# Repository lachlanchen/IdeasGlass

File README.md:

[English](README.md) · [العربية](i18n/README.ar.md) · [Español](i18n/README.es.md) · [Français](i18n/README.fr.md) · [日本語](i18n/README.ja.md) · [한국어](i18n/README.ko.md) · [Tiếng Việt](i18n/README.vi.md) · [中文 (简体)](i18n/README.zh-Hans.md) · [中文（繁體）](i18n/README.zh-Hant.md) · [Deutsch](i18n/README.de.md) · [Русский](i18n/README.ru.md)

# IdeasGlass

*A wearable AI glass that turns ideas into actions, income, and creative momentum.*

> Voice-first wearable AI pipeline: capture from ESP32 glasses, process in FastAPI, and monitor/control via a live PWA dashboard.

| Lane | Purpose |
|---|---|
| 🎙️ Wearable capture | ESP32 glasses send audio, photos, and telemetry in near-real-time |
| 🧠 Backend intelligence | FastAPI ingests streams, transcribes, segments, and persists metadata |
| 🖥️ Dashboard | PWA shows live waveform, transcripts, and device/account status |

<div align="center">

  <br/>
  <sub>App UI (left) · Hardware (right)</sub>
</div>

Explore community experiments at <a href="https://onlyideas.art">onlyideas.art</a>.

## 🚀 Overview

IdeasGlass is an AI-first wearable system for voice-first idea capture and execution. In this repository, the primary runtime path is:

- `backend/glass/` for FastAPI APIs, WebSocket ingest, Whisper-based transcription, and the installable PWA dashboard.
- `IdeaGlass/firmware/ideasglass_arduino/IdeasGlassClient/` for XIAO ESP32S3 firmware streaming telemetry/audio/photos.

If you are new to this repo, start there first.

## 📚 Table of Contents

- [🚀 Overview](#-overview)
- [✨ Why IdeasGlass](#-why-ideasglass)
- [🧩 Features](#-features)
- [🔄 Sample Workflow](#-sample-workflow)
- [🗂️ Project Structure](#-project-structure)
- [🧰 Prerequisites](#-prerequisites)
- [⚙️ Installation](#️-installation)
- [▶️ Usage](#️-usage)
- [🛠️ Configuration](#️-configuration)
- [🧪 Examples](#-examples)
- [🧭 Development Notes](#-development-notes)
- [🆘 Troubleshooting](#️-troubleshooting)
- [🌐 Ecosystem Links](#-ecosystem-links)
- [🙏 Acknowledgements](#-acknowledgements)
- [🛣️ Roadmap](#️-roadmap)
- [🤝 Contribution](#-contribution)
- [❤️ Support](#-support)
- [📄 License](#-license)

### At a glance

| Area | Primary location | What it does |
|---|---|---|
| Backend API + PWA | `backend/glass/` | FastAPI endpoints, WebSocket ingest/fanout, transcription, dashboard |
| Firmware | `IdeaGlass/firmware/ideasglass_arduino/IdeasGlassClient/` | ESP32 capture/streaming client |
| Bridge notes | `references/ideasglass_bridge.md` | TLS/WAN reliability notes and deployment field tips |
| README translations | `i18n/` | Multilingual docs synced from the canonical README |

## ✨ Why IdeasGlass

IdeasGlass is an AI-first wearable built for people who live in streams of ideas. It captures, translates, organizes, and executes on creativity the moment inspiration strikes, whether you are narrating a concept in motion or hosting a live session.

## 🧩 Features

### Product vision features

- **Creation-native hardware** – lightweight glasses and wearable inputs, tuned for voice-first capture plus subtle gesture shortcuts.
- **Instant translation** – real-time language detection/translation so you can ideate across teams or audiences without switching tools.
- **EchoMind co-pilot** – tight pairing with `chat.lazying.art` for brainstorming, script drafting, and multilingual content coaching.
- **Channel autopilot** – drafts outlines, long-form scripts, short-form hooks, and schedules uploads to YouTube or other feeds.
- **Highlights & reels** – auto-selects moments, generates thumbnails, subtitles, and social-ready clips.
- **Income layer** – connects to LazyingArt Coin for tipping, credit payouts, and conversion to on-chain assets.
- **Spending & focus** – tracks operational spend, surfaces profitable formats, and distills your personal strengths into next projects.

### Repository/runtime features

- FastAPI backend with REST + WebSocket endpoints for ingest (`/api/v1/audio`, `/ws/audio-ingest`) and live stream fanout (`/ws/stream`).
- Deterministic audio segmentation (default ~15 s with overlap) into `backend/glass/audio_segments/`.
- Optional openai-whisper streaming transcripts with configurable latency thresholds.
- Optional Postgres persistence (`DATABASE_URL`) for messages, photos, chunks, segments, transcripts.
- PWA dashboard with live waveform, transcript updates, and install support on desktop/mobile.
- Arduino firmware support for XIAO ESP32S3 Sense camera + mic flows.

## 🔄 Sample Workflow

1. **Capture** – Speak or sketch a concept; IdeasGlass transcribes, translates, and tags the intent.
2. **Co-create** – EchoMind refines the idea, drafts scripts, and suggests CTAs tailored for each platform.
3. **Publish** – The channel agent auto-produces highlight videos, gallery images, and uploads them with metadata.
4. **Monetize** – Credits route through LazyingArt Coin (`coin.lazying.art`) and payouts sync with your preferred wallets.
5. **Reflect** – Spending, reach, and engagement dashboards surface what to double down on next.

## 🗂️ Project Structure

```text
IdeasGlass/
├── README.md
├── i18n/                                  # README translations
├── backend/
│   ├── glass/                             # Primary FastAPI + PWA backend
│   │   ├── app.py
│   │   ├── serve.py
│   │   ├── requirements.txt
│   │   ├── static/
│   │   ├── tools/
│   │   └── audio_segments/
│   ├── tornado_app/                       # Secondary/parallel ingest backend path
│   ├── memo/
│   ├── memo_legacy/
│   └── ngrok_bridge/
├── IdeaGlass/firmware/ideasglass_arduino/
│   ├── IdeasGlassClient/
│   ├── config.h
│   ├── WifiTest/WifiTest.ino
│   ├── wifi_credentials.example.h
│   └── README.md
├── references/ideasglass_bridge.md        # Bridge + deployment notes
├── docs/                                  # Additional site/docs assets
├── development_plan/
├── app/
├── ops/observability/
├── ios-app-example/
├── figs/
├── seeed_studio_xiao_esp32s3_dev/
└── .auto-readme-work/
```

## 🧰 Prerequisites

- Python 3.10+
- `pip` (or conda environment with compatible Python)
- Optional: NVIDIA GPU + CUDA/cuDNN for faster Whisper inference
- Optional: PostgreSQL for persistence
- For firmware: Arduino IDE or `arduino-cli`, Seeed XIAO ESP32S3 Sense, PSRAM enabled

| Component | Requirement | Notes |
|---|---|---|
| Backend runtime | Python 3.10+, `pip` | Use venv or conda (`glass`) |
| GPU acceleration (optional) | NVIDIA + CUDA/cuDNN | Improves Whisper latency |
| Persistence (optional) | PostgreSQL | Enabled via `DATABASE_URL` |
| Firmware toolchain | Arduino IDE / `arduino-cli` | Use XIAO ESP32S3 profile with PSRAM |

## ⚙️ Installation

### Backend dependencies

```bash
cd backend/glass
python -m venv .venv
source .venv/bin/activate
pip install -r requirements.txt
```

### Firmware prerequisites

- Copy `IdeaGlass/firmware/ideasglass_arduino/wifi_credentials.example.h` to `wifi_credentials.h` (recommended) and set SSID/password.
- In Arduino IDE, use board `ESP32 -> XIAO_ESP32S3` with `PSRAM: OPI PSRAM`.
- Partition scheme: `Default with spiffs (3MB APP/1.5MB SPIFFS)` or `Maximum APP` when filesystem is not needed.

## ▶️ Usage

### Run backend (uvicorn)

```bash
IDEASGLASS_WHISPER_MODEL=base IDEASGLASS_WHISPER_DEVICE=cuda \
uvicorn backend.glass.app:app \
  --host 0.0.0.0 \
  --port 8765 \
  --proxy-headers \
  --forwarded-allow-ips="*" \
  --reload
```

### Run backend (helper)

```bash
python backend/glass/serve.py --whisper-model base --whisper-device cuda --reload
```

### Open dashboard

- `http://localhost:8765/`
- `http://localhost:8765/healthz`

| Endpoint | Purpose |
|---|---|
| `/` | Main dashboard (PWA-capable UI) |
| `/healthz` | Backend liveness check |
| `/ws/audio-ingest` | Device ingest WebSocket |
| `/ws/stream` | Live stream fanout to dashboard clients |

### Login and bind your device

1. Register or login from the dashboard Settings/Account area.
2. Bind your device ID in the `Bind device` field.
3. Only bound devices will stream to your account.

Generate a device ID + QR image:

```bash
python backend/glass/tools/generate_device_id.py --out logs/device-id.png
```

Bind through API (cookie session required):

```bash
curl -X POST http://localhost:8765/api/v1/devices/bind \
  -H 'Content-Type: application/json' \
  -d '{"device_id":"<your-device-id>"}' \
  -b cookies.txt -c cookies.txt
```

Verify current account and bound devices:

```bash
curl -s http://localhost:8765/api/v1/auth/me -b cookies.txt -c cookies.txt | jq
```

Optional migration (rename historical data to a new device ID):

```bash
curl -X POST http://localhost:8765/api/v1/devices/rename \
  -H 'Content-Type: application/json' \
  -d '{"from_id":"old-id","to_id":"<your-device-id>"}' \
  -b cookies.txt -c cookies.txt
```

### Firmware build/upload (Arduino CLI)

```bash
FQBN='esp32:esp32:XIAO_ESP32S3:PartitionScheme=default_8MB,PSRAM=opi'
SKETCH='IdeaGlass/firmware/ideasglass_arduino/IdeasGlassClient'
PORT='/dev/ttyACM0'

bin/arduino-cli compile --fqbn "$FQBN" "$SKETCH"
bin/arduino-cli upload -p "$PORT" --fqbn "$FQBN" "$SKETCH"
```

If port is busy: `fuser -k /dev/ttyACM0`.
If permission denied: `sudo usermod -aG dialout $USER` then re-login (or temporary `sudo chmod a+rw /dev/ttyACM0`).

### Firmware power UX (XIAO ESP32S3)

- Hold the button ~0.8 s at power-up to boot.
- Hold ~2.5 s while running to enter deep sleep.
- Short press while running still triggers capture.

## 🛠️ Configuration

### Core environment variables

- `DATABASE_URL`: optional Postgres DSN for persistent storage.
- `IDEASGLASS_WHISPER_MODEL`: `base` (default), `small`, `medium`, `large-v3`, `large-v3-turbo`.
- `IDEASGLASS_WHISPER_DEVICE`: `cuda` or `cpu`.
- `IDEASGLASS_WHISPER_FP16`: `1` for GPU mixed precision, `0` for CPU.
- `IDEASGLASS_TRANSCRIBE`: `1` (default) to enable transcription, `0` to disable.
- `IDEASGLASS_TRANSCRIPT_INTERVAL_MS`: rolling transcript interval.
- `IDEASGLASS_TRANSCRIPT_THRESHOLDS_MS`: comma-separated thresholds (default `3000,6000,15000`).

| Variable | Default / options | Effect |
|---|---|---|
| `DATABASE_URL` | unset by default | Enables Postgres persistence for account/device data |
| `IDEASGLASS_WHISPER_MODEL` | `base` (`small`, `medium`, `large-v3`, `large-v3-turbo`) | Controls accuracy vs latency |
| `IDEASGLASS_WHISPER_DEVICE` | `cuda` or `cpu` | Inference backend |
| `IDEASGLASS_WHISPER_FP16` | `1` GPU, `0` CPU-safe | Mixed precision control |
| `IDEASGLASS_TRANSCRIBE` | `1` | Toggle transcription pipeline |
| `IDEASGLASS_TRANSCRIPT_INTERVAL_MS` | runtime configured | Rolling transcript push interval |
| `IDEASGLASS_TRANSCRIPT_THRESHOLDS_MS` | `3000,6000,15000` | Progressive transcript emission thresholds |

Safe `DATABASE_URL` examples:

- `export DATABASE_URL="postgresql://<db_user>@localhost/ideasglass_db"` (peer/local auth)
- `export DATABASE_URL="postgresql://<db_user>:<db_password>@localhost/ideasglass_db"` (password auth)

### Audio gain and segmentation knobs

- `IDEASGLASS_GAIN_TARGET` (default `0.032`)
- `IDEASGLASS_GAIN_MAX` (default `1.8`)
- `IDEASGLASS_GAIN_MIN_RMS` (default `0.008`)
- `IDEASGLASS_SPEECH_RMS` (default `0.03`)
- `IDEASGLASS_SPEECH_MARGIN` (default `0.005`)
- `IDEASGLASS_SEGMENT_TARGET_MS` (default `15000`)
- `IDEASGLASS_SEGMENT_OVERLAP_MS` (default `2000`)
- `IDEASGLASS_SEGMENT_GAIN_TARGET` (defaults to chunk gain target)

| Audio knob | Default | Purpose |
|---|---|---|
| `IDEASGLASS_GAIN_TARGET` | `0.032` | Target RMS normalization |
| `IDEASGLASS_GAIN_MAX` | `1.8` | Upper clamp for gain amplification |
| `IDEASGLASS_GAIN_MIN_RMS` | `0.008` | Floor to avoid amplifying near-silence |
| `IDEASGLASS_SPEECH_RMS` | `0.03` | Speech activity RMS baseline |
| `IDEASGLASS_SPEECH_MARGIN` | `0.005` | Margin around speech threshold |
| `IDEASGLASS_SEGMENT_TARGET_MS` | `15000` | Segment length target |
| `IDEASGLASS_SEGMENT_OVERLAP_MS` | `2000` | Segment overlap for continuity |
| `IDEASGLASS_SEGMENT_GAIN_TARGET` | inherits chunk gain | Segment-level normalization target |

### Model prefetch (optional)

```bash
python backend/glass/tools/prefetch_whisper_models.py \
  --models tiny,base,small,medium,large-v3 \
  --device cuda \
  --fp16 1
```

## 🧪 Examples

### Generate and bind a device ID

```bash
python backend/glass/tools/generate_device_id.py --out logs/device-id.png
```

Then set `kDeviceId` in:

- `IdeaGlass/firmware/ideasglass_arduino/IdeasGlassClient/IdeasGlassClient.ino`

Dashboard flow:

1. Register/login in Settings.
2. Bind the device in the Account panel.
3. Only bound devices stream to your account.

### REST ingest examples

```bash
curl -X POST http://localhost:8765/api/v1/messages \
  -H 'Content-Type: application/json' \
  -d '{"device_id":"dev-001","message":"hello from curl"}'
```

```bash
curl -X POST http://localhost:8765/api/v1/messages \
  -H 'Content-Type: application/json' \
  -d '{
    "device_id":"dev-001",
    "message":"photo demo",
    "photo_base64":"'"$(base64 -w0 sample.jpg)'"',
    "photo_mime":"image/jpeg"
  }'
```

```bash
rec --bits 16 --channels 1 --rate 16000 -c 1 -b 16 -e signed-integer temp.raw trim 0 0.25
curl -X POST http://localhost:8765/api/v1/audio \
  -H 'Content-Type: application/json' \
  -d '{
    "device_id":"dev-001",
    "sample_rate":16000,
    "bits_per_sample":16,
    "duration_ms":250,
    "rms":0.05,
    "audio_base64":"'"$(base64 -w0 temp.raw)'"'
  }'
```

```bash
curl http://localhost:8765/api/v1/audio/segments | jq '.[0]'
curl -o latest.wav http://localhost:8765/api/v1/audio/segments/<segment-id>
```

## 🧭 Development Notes

### Focus area

This repo contains multiple backend tracks. Current contributor guidance and runtime focus is `backend/glass/` unless otherwise requested.

### Static/syntax check

```bash
python -m compileall backend/glass/app.py
```

### Developer docs

- [IdeasGlass Object Analysis](OmiGlass/docs/ideasglass_analysis.mdx)
- [Arduino Hardware Blueprint](OmiGlass/docs/ideasglass_arduino_hardware.md)
- [Multi-platform App / PWA Plan](OmiGlass/docs/ideasglass_pwa_plan.md)
- [Bridge & Arduino HTTPS Client](docs/ideasglass_bridge.md)

> Note: In the current repository snapshot, some historical links above appear to have moved (for example, bridge notes now exist at `references/ideasglass_bridge.md`). The original links are preserved as canonical README content.

### Quick device binding (preserved workflow)

- Generate ID (in conda `glass`): `python backend/glass/tools/generate_device_id.py`
- Set it in firmware: `IdeaGlass/firmware/ideasglass_arduino/IdeasGlassClient/IdeasGlassClient.ino` (`kDeviceId`)
- Run backend and open `http://localhost:8765`, register/login, then bind the device ID in the Account panel

## 🆘 Troubleshooting

- **Port already in use:** run backend on another port and update client settings.
- **Serial port busy:** `fuser -k /dev/ttyACM0`.
- **Linux serial permission denied:** `sudo usermod -aG dialout $USER` and re-login.
- **Postgres unavailable:** backend can run without DB for partial functionality; verify `DATABASE_URL` and restart.
- **Whisper performance issues:** use smaller models (`base`/`small`) or disable transcription via `IDEASGLASS_TRANSCRIBE=0`.
- **TLS/time sync instability on ESP32:** verify Wi-Fi, NTP availability (UDP/123), and cert/host settings; see `references/ideasglass_bridge.md` for detailed field notes.
- **No live waveform updates:** check backend logs and browser console for `[IdeasGlass][wave]` traces and confirm `/ws/stream` connectivity.

## 🌐 Ecosystem Links

| Brand | Purpose | Link |
|---|---|---|
| 🧠 EchoMind | Multilingual AI companion for learning and creation | [chat.lazying.art](https://chat.lazying.art) |
| 🌱 OnlyIdeas | Research-to-product community for bold concepts | [onlyideas.art](https://onlyideas.art) |
| 💸 LazyEarn | Automations to turn small wins into income | [earn.lazying.art](https://earn.lazying.art) |
| 📚 LazyLearn | Physics & chemistry tracks and notebooks | [learn.lazying.art](https://learn.lazying.art) |
| 🤖 IdeasRobot | Agent that turns ideas into drafts, tasks, and posts | [robot.lazying.art](https://robot.lazying.art) |
| 👓 IdeasGlass | Capture, translate, and auto-produce highlight reels | [glass.lazying.art](https://glass.lazying.art) |
| 🪙 LazyingArt Coin | Rewards and payouts bridging contributions and on-chain value | [coin.lazying.art](https://coin.lazying.art) |
| 🧪 IDEAS | Notebook of research notes and essays | [ideas.onlyideas.art](https://ideas.onlyideas.art) |
| 🎨 LazyingArt | Studio behind OnlyIdeas, EchoMind, LazyEdit, and IdeasGlass | [lazying.art](https://lazying.art) |

## 🙏 Acknowledgements

We stand on the shoulders of great open projects — thank you to:

- <a href="https://www.omi.me/?ref=LazyingArt" target="_blank" rel="noopener" style="display:inline-flex;align-items:center;justify-content:center;padding:0.45rem 1rem;border-radius:999px;background:#111827;color:#ffffff;font-weight:700;text-decoration:none;">Get OmiGlass (BasedHardware)</a>
  - **Referral Program** — Use coupon `LazyingArt` to save 10% (30% commission unlocks after 10 sales).

    <div style="display:flex;flex-wrap:wrap;gap:0.4rem;margin:0.3rem 0;">
      <a href="https://www.omi.me/?ref=LazyingArt" target="_blank" rel="noopener" style="display:inline-flex;align-items:center;justify-content:center;padding:0.45rem 1.1rem;border-radius:999px;background:#111827;color:#ffffff;font-weight:700;text-decoration:none;">Get OmiGlass with LazyingArt</a>
      <a href="https://discord.com/invite/8MP3b9ymvx?ref=LazyingArt" target="_blank" rel="noopener" style="display:inline-flex;align-items:center;justify-content:center;padding:0.45rem 1rem;border-radius:999px;background:#2563eb;color:#ffffff;font-weight:700;text-decoration:none;">Join Omi Discord</a>
      <a href="https://www.seeedstudio.com/Seeed-XIAO-BLE-Sense-nRF52840-p-5253.html" target="_blank" rel="noopener" style="display:inline-flex;align-items:center;justify-content:center;padding:0.45rem 1rem;border-radius:999px;background:#059669;color:#ffffff;font-weight:700;text-decoration:none;">Buy Seeed XIAO BLE Sense</a>
    </div>
- OpenAI Whisper: https://github.com/openai/whisper
- WhisperX: https://github.com/m-bain/whisperX
- Ollama: https://github.com/ollama/ollama

## 🛣️ Roadmap

- Harden and document the end-to-end audio streaming path across WAN/TLS environments.
- Continue improving transcript quality/latency tradeoffs (model/device/threshold presets).
- Expand device management and account-scoped multi-device workflows in the dashboard.
- Align or consolidate legacy/parallel backend tracks (`tornado_app`, `memo`, `memo_legacy`, `ngrok_bridge`) with the primary `backend/glass` path.
- Maintain and refresh multilingual README variants under `i18n/`.

## 🤝 Contribution

Contributions are welcome. For repository-specific workflow guidance, follow `AGENTS.md`.

Recommended local validation before opening a PR:

```bash
python -m compileall backend/glass/app.py
```

When submitting changes:

- Keep commit subjects short and action-driven (present tense).
- Mention relevant env vars (for example `IDEASGLASS_TRANSCRIPT_THRESHOLDS_MS`) in PR notes when behavior depends on them.
- Include testing evidence (backend logs, dashboard behavior, firmware output).
- Never commit secrets (`DATABASE_URL`, API tokens, credentials files).

## ❤️ Support

<!-- support:start -->

<!-- support:end -->

## 📄 License

No top-level `LICENSE` file was detected in this repository snapshot. Until an explicit license file is added, treat usage and redistribution as requiring maintainer approval.

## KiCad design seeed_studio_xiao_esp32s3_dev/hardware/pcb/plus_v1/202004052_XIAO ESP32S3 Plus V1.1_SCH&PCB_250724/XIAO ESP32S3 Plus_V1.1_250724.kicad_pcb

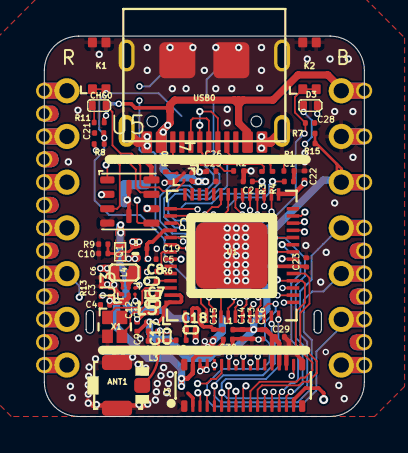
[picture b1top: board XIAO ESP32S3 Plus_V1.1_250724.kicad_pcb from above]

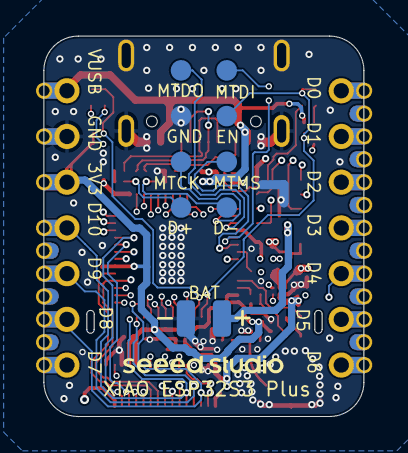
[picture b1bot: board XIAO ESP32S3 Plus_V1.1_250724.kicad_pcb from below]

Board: 6 copper layers, 17.8 x 21.1 mm, 70 parts (10 on the bottom side), 62 nets.

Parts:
ANT1: U.FL-R-SMT-1; U-FL3P-SMD-2.6X2.6X1.0MM
BAT0: VBAT; TP-80X40MIL
C1, C2, C20: DNP; C0201
C3, C9, C13, C16: 2.2uF; C0201
C4, C5, C6: 4.7uF; C0201
C7, C8: 12pF; C0201
C10, C21, C25, C26: 1uF; C0201
C11, C14, C15, C19, C22, C23, C29, C30: 100nF; C0201
C12: 10nF; C0201
C17: 1.2pF; C0201
C18: 1.8pF; C0201
C28: 10pF; C0201
CHG0: RED; LED-0402
D2: LMBR4010BST5G; DFN1006-2L
D3: Yellow; LED-0402
GND0: GND; TP-80X40MIL
J3: 30pin; BTB30-0.4-7.52X2.97X1.14
K1, K2: SKTAAAE010/311021459; SW4-SMD-2.8-2.6X1.6X0.53MM
L1: 2nH; L0201
L2: 3.3nH; L0201
L3: DNP; L0201
L4: 470nH; L0603
L5: 24nH; L0201
Q1: PMOS_1.00.60.35MM; PMOS_1.0*0.6*0.35MM
R1, R2: 5.1K; R0201
R3, R4: 22R; R0201
R6: 499R; R0201
R7, R8, R11: 10K; R0201
R9: 100K; C0201
R10: 220K; R0201
R13: 249K; R0201
R15: 1.5K; R0201
TP1, TP2, TP3, TP4, TP5, TP6, TP7, TP8: TEST-POINT'4545'; TP-D45MIL
U1: MCU-ESP32-S3; QFN56G-0.4-7X7MM
U2: XIAO-HALF-HOLE-23P; MOUDLE23P-XIAO-HALF-HOLE
U3: SGM6029CYG/TR; BGA6-0.35-0.85X1.2X0.4MM
U4: SGM40567-4.2XG/TR; WLCSP-0.4-0.92X1.16X0.4MM
U5: PY25Q128HA-DFH-IR; USON8-0.8-3X3X0.55MM
USB0: UBF31-0171; USB2.0-TYPE-C
X1: 40MHz; X4-SMD-1.6X1.2X0.35MM

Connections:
/D0/A0: U1.6 (GPIO1), U2.1 (GPIO1_D0/A0)
/D1/A1: U1.7 (GPIO2), U2.2 (GPIO2_D1/A1)
/D2/A2: J3.2, U1.8 (GPIO3), U2.3 (GPIO3_D2/A2)
/D3/A3: U1.9 (GPIO4), U2.4 (GPIO4_D3/A3)
/D4/A4/I2C_SDA: U1.10 (GPIO5), U2.5 (GPIO5_D4/A4/I2C_SDA)
/D5/A5/I2C_SCL: U1.11 (GPIO6), U2.6 (GPIO6_D5/A5/I2C_SCL)
/D6/TX: R6.2, U2.7 (U0TXD_D6/TX)
/D7/RX: U1.50 (U0RXD), U2.8 (U0RXD_D7/RX)
/D8/A8/SCK: J3.3, U1.12 (GPIO7), U2.9 (GPIO7_D8/A8/SCK)
/D9/A9/MISO: J3.4, U1.13 (GPIO8), U2.10 (GPIO8_D9/A9/MISO)
/D10/A10/MOSI: J3.5, U1.14 (GPIO9), U2.11 (GPIO9_D10/A10/MOSI)
/EN: C21.2, K1.1 (A0), K1.3 (A1), R8.1, TP6.T, U1.4 (CHIP_PU)
/ESP_USB_D+: C1.2, R4.2, TP8.T, U1.26 (GPIO20)
/ESP_USB_D-: C2.2, R3.2, TP7.T, U1.25 (GPIO19)
/GPIO0: C28.2, K2.1 (A0), K2.3 (A1), R7.1, U1.5 (GPIO0)
/IO10/XMCLK/ADC_BAT: J3.6, U1.15 (GPIO10), U2.20 (GPIO10_XMCLK/ADC_BAT)
/IO11/DVP_Y8/SPI_MOSI1: J3.7, U1.16 (GPIO11), U2.21 (GPIO11_DVP_Y8/SPI_MOSI1)
/IO12/DVP_Y7/SPI_MISO1: J3.8, U1.17 (GPIO12), U2.22 (GPIO12_DVP_Y7/SPI_MISO1)
/IO13/DVP_PCLK/SPI_SCK1: J3.9, U1.18 (GPIO13), U2.23 (GPIO13_DVP_PCLK/SPI_SCK1)
/IO14/DVP_Y6: J3.10, U1.19 (GPIO14)
/IO15/DVP_Y2: J3.11, U1.21 (XTAL_32K_P)
/IO16/DVP_Y5: J3.12, U1.22 (XTAL_32K_N)
/IO17/DVP_Y3: J3.13, U1.23 (GPIO17)
/IO18/DVP_Y4: J3.14, U1.24 (GPIO18)
/IO21/USER_LED: D3.-, J3.16, U1.27 (GPIO21)
/IO38/DVP_VSYNC/I2S_SD: J3.23, U1.43 (GPIO38), U2.15 (GPIO38_DVP_VSYNC/I2S_SD)
/IO47/DVP_HREF: J3.22, U1.37 (SPICLK_P)
/IO48/DVP_Y9: J3.21, U1.36 (SPICLK_N)
/MTCK/IO39/CAM_SCL/I2S_SCK: J3.24, TP5.T, U1.44 (MTCK), U2.16 (GPIO39_CAM_SCL/I2S_SCK)
/MTDI/IO41/PDM_DATA/RX1: J3.26, TP3.T, U1.47 (MTDI), U2.18 (GPIO41_PDM_DATA/RX1)
/MTDO/IO40/CAM_SDA/I2S_WS: J3.25, TP4.T, U1.45 (MTDO), U2.17 (GPIO40_CAM_SDA/I2S_WS)
/MTMS/IO42/PDM_CLK/TX1: J3.27, TP2.T, U1.48 (MTMS), U2.19 (GPIO42_PDM_CLK/TX1)
/SPICLK: U1.33 (SPICLK), U5.6 (SCLK)
/SPICS0: U1.32 (SPICS0), U5.1 (CS#)
/SPID: U1.35 (SPID), U5.5 (SI)
/SPIHD: U1.30 (SPIHD), U5.7 (HOLD#/RESET#)
/SPIQ: U1.34 (SPIQ), U5.2 (SO)
/SPIWP: U1.31 (SPIWP), U5.3 (WP#)
/USB_D+: R4.1, USB0.A6 (A6/DP1), USB0.B6 (B6/DP2)
/USB_D-: R3.1, USB0.A7 (A7/DN1), USB0.B7 (B7/DN2)
/VBAT: BAT0.1 (T), C26.1, Q1.1 (D), U4.A1 (BAT)
/VBUS: C10.1, C25.1, D2.+, Q1.2 (G), R9.2, R11.1, U2.14 (VBUS), U4.A2 (VIN), USB0.A4_B9 (A4/B9/VBUS), USB0.B4_A9 (B4/A9/VBUS)
/VCC_3V3: C5.2, C6.2, C9.2, C11.2, C12.2, C13.2, C14.2, C16.2, C19.2, C23.1, C29.2, J3.18, J3.19, L1.1, L4.2, R7.2, R8.2, R15.2, U1.20 (VDD3P3_RTC), U1.46 (VDD3P3_CPU), U1.55 (VDDA@1), U1.56 (VDDA@2), U2.12 (VCC_3V3), U3.A2 (VOS)
/VDD_SPI: C22.2, U1.29 (VDD_SPI), U5.8 (VCC)
/VIN: C3.1, C4.1, C30.2, D2.-, J3.15, J3.30, Q1.3 (S), U3.B1 (VIN), U3.C2 (EN)
GND_POWER: ANT1.GND1, ANT1.GND2, C1.1, C2.1, C3.2, C4.2, C5.1, C6.1, C7.2, C8.1, C9.1, C10.2, C11.1, C12.1, C13.1, C14.1, C15.1, C16.1, C17.2, C18.2, C19.1, C20.1, C21.1, C22.1, C23.2, C25.2, C26.2, C28.1, C29.1, C30.1, GND0.1 (T), J3.17, J3.28, J3.29, J3.31, J3.33, J3.34, K1.2 (B0), K1.4 (B1), K2.2 (B0), K2.4 (B1), R1.1, R2.2, R9.1, R10.1, R13.1, TP1.T, U1.57 (GND), U2.13 (GND), U3.A1 (GND), U4.B1 (F), U4.C2 (GND), U5.4 (GND), U5.9 (GND), U5.10 (GND), USB0.A1_B12 (A1/B12/GND), USB0.B1_A12 (B1/A12/GND), USB0.S1, USB0.S2, USB0.S3, USB0.S4, USB0.S5 (S1), USB0.S6 (S2), X1.2 (GND), X1.4 (GND@1)
unnamed: ANT1.D, C17.1, L2.1, L3.2
unnamed: C20.2, L3.1
unnamed: CHG0.+, R11.2
unnamed: D3.+, R15.1
unnamed: C18.1, L2.2, U1.1 (LNA_IN)
unnamed: R6.1, U1.49 (U0TXD)
unnamed: C15.2, L1.2, U1.2 (VDD3P3@1), U1.3 (VDD3P3@2)
unnamed: C8.2, U1.53 (XTAL_N), X1.1 (X1)
unnamed: L5.1, U1.54 (XTAL_P)
unnamed: R13.2, U3.C1 (MODE)
unnamed: L4.1, U3.B2 (SW)
unnamed: R10.2, U4.C1 (IREF)
unnamed: CHG0.-, U4.B2 (NCHG)
unnamed: R1.2, USB0.A5 (A5/CC1)
unnamed: R2.1, USB0.B5 (B5/CC2)
unnamed: C7.1, L5.2, X1.3 (X2)

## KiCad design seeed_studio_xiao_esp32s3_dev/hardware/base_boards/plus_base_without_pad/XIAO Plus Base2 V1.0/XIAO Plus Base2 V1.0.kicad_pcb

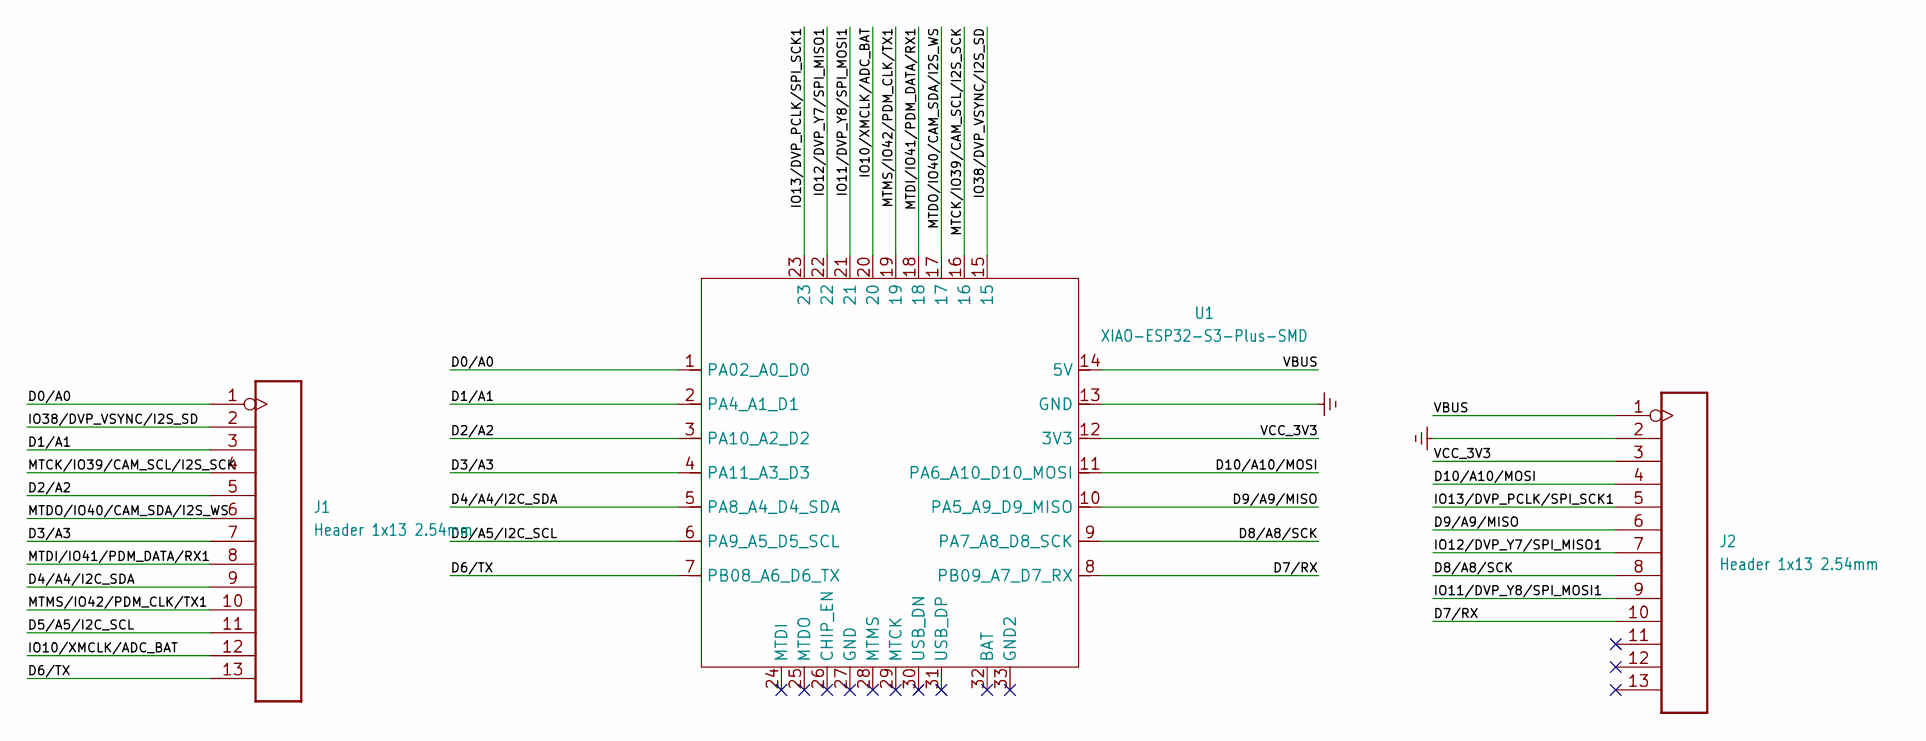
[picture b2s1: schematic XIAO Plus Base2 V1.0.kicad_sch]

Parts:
J1, J2: Header 1x13 2.54mm; H13-2.54-35; Part Type Header
U1: XIAO-ESP32-S3-Plus-SMD

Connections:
/D0/A0: J1.1, U1.1 (PA02_A0_D0)
/D1/A1: J1.3, U1.2 (PA4_A1_D1)
/D2/A2: J1.5, U1.3 (PA10_A2_D2)
/D3/A3: J1.7, U1.4 (PA11_A3_D3)
/D4/A4/I2C_SDA: J1.9, U1.5 (PA8_A4_D4_SDA)
/D5/A5/I2C_SCL: J1.11, U1.6 (PA9_A5_D5_SCL)
/D6/TX: J1.13 (11), U1.7 (PB08_A6_D6_TX)
/D7/RX: J2.10, U1.8 (PB09_A7_D7_RX)
/D8/A8/SCK: J2.8, U1.9 (PA7_A8_D8_SCK)
/D9/A9/MISO: J2.6, U1.10 (PA5_A9_D9_MISO)
/D10/A10/MOSI: J2.4, U1.11 (PA6_A10_D10_MOSI)
/IO10/XMCLK/ADC_BAT: J1.12 (11), U1.20
/IO11/DVP_Y8/SPI_MOSI1: J2.9, U1.21
/IO12/DVP_Y7/SPI_MISO1: J2.7, U1.22
/IO13/DVP_PCLK/SPI_SCK1: J2.5, U1.23
/IO38/DVP_VSYNC/I2S_SD: J1.2, U1.15
/MTCK/IO39/CAM_SCL/I2S_SCK: J1.4, U1.16
/MTDI/IO41/PDM_DATA/RX1: J1.8, U1.18
/MTDO/IO40/CAM_SDA/I2S_WS: J1.6, U1.17
/MTMS/IO42/PDM_CLK/TX1: J1.10, U1.19
/VBUS: J2.1, U1.14 (5V)
/VCC_3V3: J2.3, U1.12 (3V3)
GND_POWER: J2.2, U1.13 (GND)

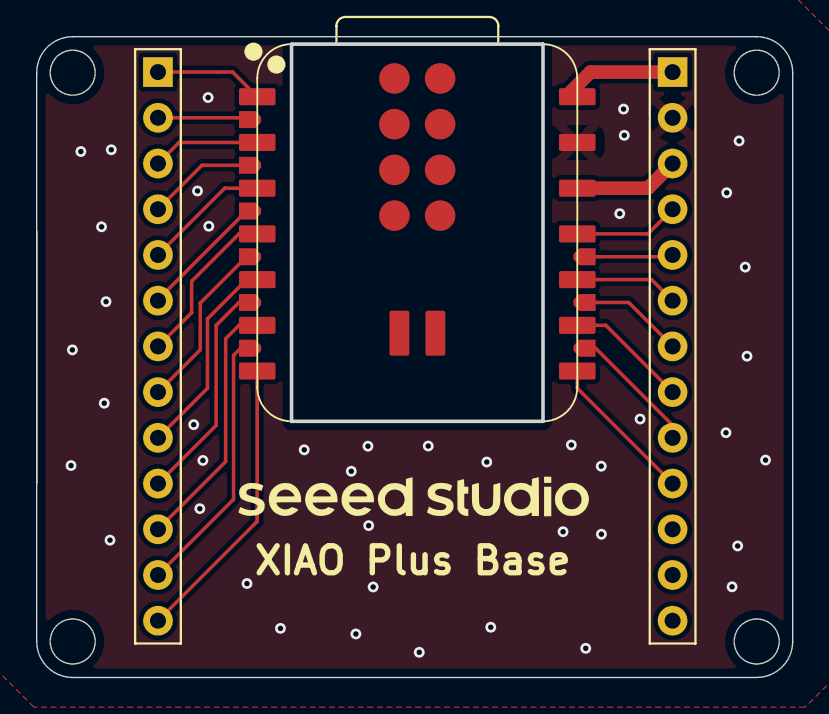
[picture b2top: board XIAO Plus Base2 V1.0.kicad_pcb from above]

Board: 2 copper layers, 42.0 x 35.6 mm, 3 parts (0 on the bottom side), 23 nets.

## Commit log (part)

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2025-11-08 docs: add initial IdeasGlass readme
2025-11-08 docs: streamline donation section
2025-11-08 Add replicated IdeasGlass assets and Seeed XIAO dev kit
2025-11-08 Fix WifiTest include path and doc instructions
2025-11-08 Ignore private workspace directory
2025-11-08 Improve WifiTest logging and network scan
2025-11-08 Add Ngrok bridge backend and Arduino HTTPS client
2025-11-08 Refresh PWA UI with light theme
2025-11-08 Handle JSONB meta when streaming history
2025-11-08 Remove unused esp_spiram include
2025-11-08 Preserve message ordering for history vs realtime
2025-11-08 Flip camera output in firmware and drop backend rotation
2025-11-08 Fix I2S pin initializer order
2025-11-08 fix: use ESP_I2S PDM capture and lengthen segments
2025-11-08 tune audio gain and speech detection
2025-11-08 shorten audio segments to 15s with overlap
2025-11-08 Add WhisperX transcription feed
2025-11-08 Stream live whisper transcripts
2025-11-08 Preload cuDNN for WhisperX
2025-11-08 Tighten whisper streaming thresholds
2025-11-08 Skip streaming transcription during silence
2025-11-08 Emit silence markers at transcript thresholds
2025-11-08 Use shared photo interval constant
2025-11-08 Log photo uploads on serial
2025-11-08 Sort in-memory messages by timestamp
2025-11-08 Optimize photo capture cadence and fix transcript/photo persistence
2025-11-08 Send photos without blocking capture
2025-11-09 Stream photos over dedicated WebSocket
2025-11-09 Add serial logger (defaults to /dev/ttyACM0)
2025-11-09 Docs: Arduino CLI + serial logging + DB correlation workflow
2025-11-09 Observability: add Grafana+Loki+Promtail stack and docs
2025-11-09 Photos: offload base64 decode and always persist in background to keep handlers responsive
2025-11-09 Fix photo_base64 decode: preserve validate=True when offloading to thread
2025-11-09 Docs: add live status verification guide (backend, serial, DB)
2025-11-09 UI: move transcripts below recordings; remove duplicate 'Recent recordings'; keep 'More' button below list
2025-11-09 Tools: add prefetch_whisper_models.py to download/load-test medium, large-v3, etc.
2025-11-09 Firmware: start chunk counter at 1; add WS connect logging, 1s heartbeat ping for photo WS, and HTTP fallback on failure
2025-11-09 Frontend: compress VU mapping and scale so bars are very short and weakly influenced by volume, per request
2025-11-09 Frontend: reduce VU saturation (noise floor=0.015, gain=11) and limit visual scale so bars don’t hit 100% under normal speech
2025-11-09 Frontend: increase VU sensitivity and visual range (gamma 0.8; baseline 25% + level*0.5) so values around 0.5 show larger height changes
2025-11-09 Frontend: add per-bar variance animator (seeded wobble) so VU shows equalizer-like movement while preserving speech vs silence levels
2025-11-09 Tools: fix whisper prefetch encode test by adding batch dimension and matching model device/dtype; fallback to encode()/transcribe on error
2025-11-09 Docs: scrub tunnel references; update paths and names to new backend/bridge and IdeasGlassClient.
2025-11-09 Deps: add email-validator (required by Pydantic EmailStr for register/login)
2025-11-09 Docs: add Device ID & Binding guide (generate ID, flash in firmware, bind via UI/API, verify via /auth/me); fix local URLs and Arduino paths
2025-11-09 Frontend: refine bottom nav (larger icons, translucent background, safe-area padding, softer active pill) and increase body bottom padding to avoid overlap
2025-11-09 UI: halve waveform height; refine Settings layout and device list; compact bottom nav spacing while keeping icons larger and unclipped
2025-11-09 Live: replace photo overlay with proper sub-page (push-style) inside Live; keep lazy-loading; compact grid with More » tile on Live
2025-11-09 UI spacing: further reduce gaps and padding between panels and within Live; tighten gallery grid spacing
2025-11-09 Fix: declare liveTranscripts* before use to avoid TDZ error; move constants to top
2025-11-09 Transcripts: microrefresh compact list to latest 5 on new final; subtle flash highlight; avoid unnecessary re-rendering.
2025-11-09 Chore: include index.html updates for Live push-pages and layout wiring.
2025-11-09 Transcripts page: add time + Play at right for each item; make list items flex with left text and right actions.
2025-11-09 Docs: add missing dashboard screenshots (ideas.lazying.art_main/full).
2025-11-09 Ignore local symlinks (whisperX, OmiGlassReference) and bridge audio output; remove symlinks from repo index.
2025-11-09 Docs: place Ecosystem and Support (Donate) side-by-side in a single row using an HTML table.
2025-11-09 Transcripts: include language code from Whisper; persist in DB; show language badge in live transcript panel and transcript detail page.
2025-11-09 Transcripts UI: show language code in compact and full transcript lists; plumb language through transcript feed and older loads.
2025-11-09 Settings/Status: place Backend status pill inline with Status title; tidy row styles to exclude header; keep WebSocket row as chip.
2025-11-09 Status UI: move Backend status to its own row under the Status title; keep header separate.
2025-11-09 Docs: convert HEIC hardware photo to PNG and add side-by-side composite with app UI (left app, right hardware).
2025-11-09 Docs: show app UI and hardware images side-by-side at full width (each half width).
2025-11-09 Docs: add Acknowledgements — OmiGlass, Whisper, WhisperX, and Ollama.
2025-11-09 Gallery: microrefresh compact gallery on new photo arrival (keeps latest tiles up to date).
2025-11-09 Firmware: add long-press power UX; archive prior Arduino sketch files under firmware/ideasglass_arduino/archived; config knobs for boot/sleep holds.
2025-11-09 Docs: document Start/Stop button UX with LED cues; enumerate button/LED and key pin map (camera, mic, I2C, battery) with tips for spare IO and RTC-wake.
2025-11-09 Firmware: fix TLS time sync + robust Wi‑Fi join; gate WS pings when offline; photo meta types as strings; keep autostart (no long‑press) for upload/charge starts
2025-11-09 Docs: record live behavior — photos smooth (HTTP fallback), audio occasional lag on WSS; add mitigation checklist and verification cues
2025-11-09 Docs: add firmware hardening plan (non-breaking) and link from bridge guide
2025-11-10 Firmware hardening (Stage A, flags off by default): add HTTP keep-alive pooling, battery ADC smoothing, lightweight counters; no behavior change unless flags enabled
2025-11-10 Firmware hardening (Stage C, flags off by default): add non-blocking WS reconnect with exponential backoff+jitter; sender never stalls; default off
2025-11-10 UI: make timer responsive — split 'Recording' and time values; wrap values to next line on small screens
2025-11-10 docs(donate): align footer with profile (centered 2-col table)
2025-11-10 UI: add 'Goal' tab to bottom nav with bullseye icon; wire up goal view and tab state persistence
2025-11-10 UI: keep 'Goal' centered by ordering tabs Live · Ideas · Goal · Creation · Settings
2025-11-10 Goals: add ig_goals DDL + /api/v1/goals (list) + /goals/seed; PWA Goal tab with elegant cards and progress bar
2025-11-10 Fix: remove stray await in setActiveTab causing SyntaxError; make populateIdeaSelect non-blocking
2025-11-10 Goals: make cards clickable to detail subpage with edit/delete; backend GET/PATCH/DELETE goal endpoints; UI form for contents
2025-11-10 Tabs: hide any open sub-pages (idea/goal/creation details, live subpages) on tab change; close modals and pause audio to prevent leaks
2025-11-10 Header: compact spacing and fixed only on Live tab; add body.header-fixed toggle in setActiveTab; reduce height/padding/gap
2025-11-10 Live header: prevent overlap and respect iPhone Dynamic Island — add viewport-fit=cover, default header-fixed class, move safe-area to header padding, body top padding only header height
2025-11-10 Subpages: hide global header on detail/More pages (adds body.hide-header toggle); ensure restored on back/tab change; respect safe-areas
2025-11-10 Header offset: measure runtime header height and set --header-offset; body top padding uses runtime offset to fully clear header across tabs and devices
2025-11-10 Prophecy Diary: add 'diary' narrative field (DDL+API+seed); center detail header title; add Prophecy section; teaser shows diary snippet; display title sans prefix
2025-11-10 Prophecy Diary vision: show richer diary-style paragraph; pre-wrap + comfortable line-height; seed with longer narrative vision
2025-11-10 Creation detail: center the main creation title (scoped to #creationDetailView)
2025-11-10 UI: add language selector (English/繁體中文/简体中文/日本語) with auto-detect, persistence, and i18n for header/nav/major labels
2025-11-10 UX: keep header fixed and scroll to top for Photos/Transcripts ‘More’ pages; stop hiding header on these subpages
2025-11-10 UI: reduce Ideas tab icon to 20x20 (only for Ideas)
2025-11-10 Settings: add Bluetooth (beta) panel with Web Bluetooth scanning on Android (Chrome/Edge), list + Bind via Device Information service when available
2025-11-10 Firmware: make long-press shutdown responsive regardless of Wi‑Fi state; preserve boot hold-to-start via config
2025-11-10 Chore: sync generated __pycache__ changes
2025-11-10 WS: accept and echo client subprotocol for /ws/audio-ingest and /ws/photo-ingest (improves compatibility with custom clients)
2025-11-10 Docs: add release note + postmortem for audio WS rollback
2025-11-10 Firmware: enable Stage A/B/C tuning flags and run Wi-Fi without modem sleep for better streaming
2025-11-10 UI: keep transcript detail header fixed at top when opened
2025-11-13 Docs: add Omi referral + quick links to README
2025-11-13 Docs: render Omi quick links as buttons
2025-11-13 Docs: use CTA button for OmiGlass + update coupon copy
2025-11-23 Docs: add GitHub Pages landing for glass.lazying.art
2025-11-23 Docs: refresh landing page with light, airy theme
2025-11-23 site: add LazyingArt ecosystem links section to IdeasGlass docs landing
2025-11-23 i18n: add language selector + English fallback; wire IdeasGlass docs to use glass.lazying.art
2025-11-23 i18n: add Simplified Chinese hero translations and MetaMask label; fix zh mapping
2025-11-23 i18n: translate IdeasGlass ecosystem section
2025-11-23 Chore: rename backend/bridge to backend/glass
2025-11-23 Docs: rename memo alias to AI Memo
2025-11-23 UI: switch Goal tab to AI Memo chat with local feed
2025-11-23 UI: make AI Memo Goal tab a full-screen chat
2025-11-23 UI: anchor AI Memo chat input above footer nav
2025-11-23 UI: fully pin AI Memo chat input above footer
2025-11-23 UI: add respond toggle and chat attach buttons, chat bubbles styled
2025-11-23 UI: hide legacy goals in Settings and remove install footer
2025-11-23 UI: per-tab header titles, hide duplicate page headings, lighten chat bar
2025-11-30 Chore: checkpoint before glass/memo reshuffle
2025-11-30 Memo nav: move Chat next to Live
2025-11-30 Memo nav: use journal-style icon for Memo tab
2025-11-30 Memo chat: default Respond toggle on
2025-11-30 Memo: generate candidate memos from chat and show confirm list
2025-11-30 Memo: add AI-backed memo suggest endpoint with OpenAI primary, DeepSeek fallback
2025-11-30 Memo: restore selected tab and reload memo candidates after refresh
2025-11-30 Memo: rely on DB-backed candidates and suggestions
2025-11-30 Memo: persist chat to DB, add AI reply injection
2025-11-30 Memo: add editable memo detail with complete/delete and chat layout tweaks
2025-11-30 Memo chat: only send new user messages to AI and show status toasts/system lines
2025-12-28 Add banner to README
2025-12-28 Update project files
2025-12-29 Update README banner
2025-12-29 Add header logo
2025-12-29 Sync ecosystem order
2026-02-28 Draft complete canonical README restructure
